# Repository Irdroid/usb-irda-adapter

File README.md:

# usb-irda-adapter
turns a USB port into an IrDA compliant infrared port for communication with IrDA devices on more recent operating systems

The USB irDA adapter is compatible with Windows 7, 10, 11 and Linux (older kernel versions, because the irDA stack was removed in recent kernel versions). 

Allows you to interface with irDA compliant devices, such as dive computers, medical instruments, power meters and more.

- Supports irDa SIR protocol (irDa spec. 1.3 )
- Supports Baud rates from 9600 to 115200
- Drivers for MS Windows 11 and 10
- USB 2.0 interface to the Host system.
- 2 meters line-of-sight irDa communication

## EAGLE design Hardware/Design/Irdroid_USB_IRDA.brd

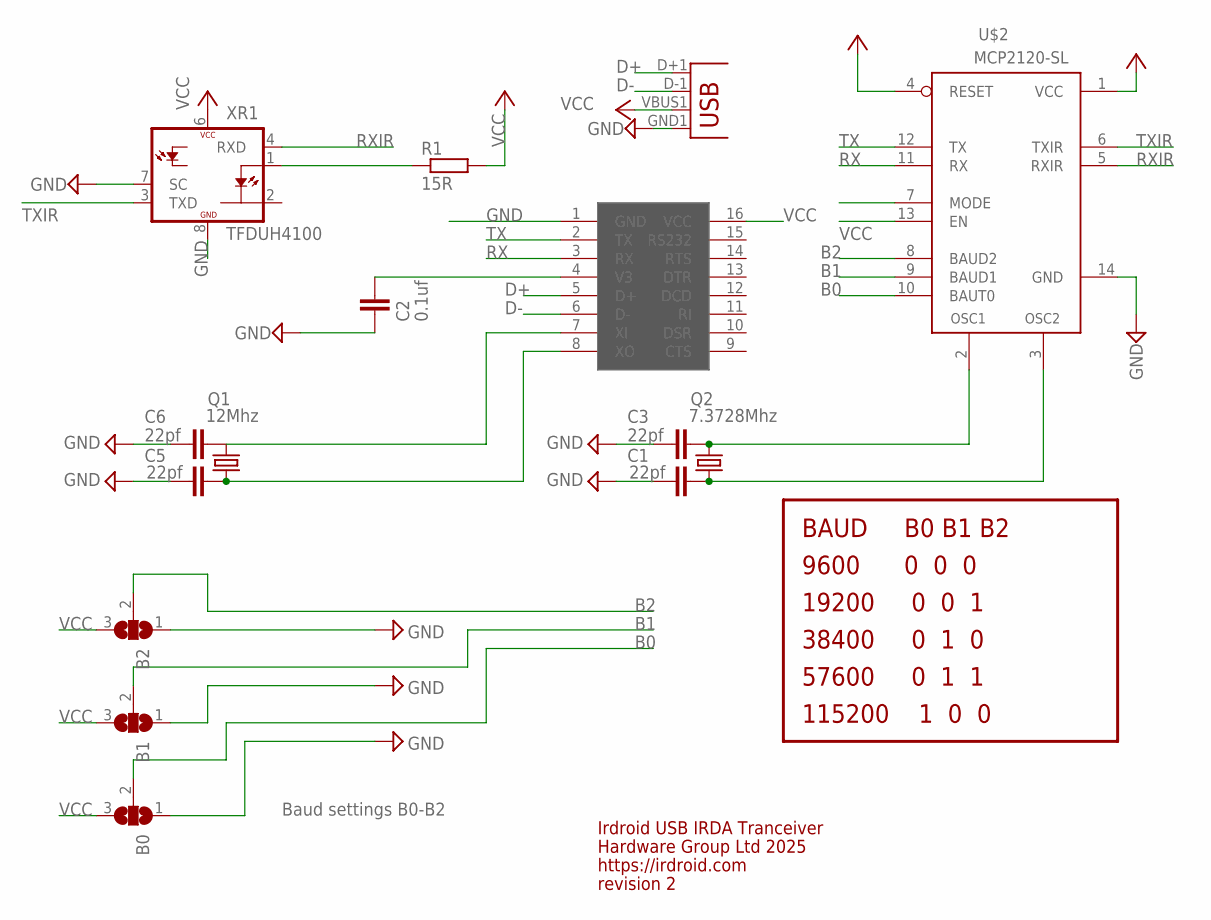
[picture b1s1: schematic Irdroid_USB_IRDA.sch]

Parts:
B0, B1, B2: SJ2W; SJ_2
C1, C3, C5, C6: 22pf; C603
C2: 0.1uf; C603
JP2: USBA-SMD-MALE; USB-A-SMT-MALE
Q1: 12Mhz; HC49UP
Q2: 7.3728Mhz; HC49UP
R1: 15R; R0603
U$1: ch; SOIC16
U$2: MCP2120-SL; SO-14
XR1: TFDUH4100; TFDU4-HOR

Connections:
B0: B0.2, U$2.10 (BAUT0)
B1: B1.2, U$2.9 (BAUD1)
B2: B2.2, U$2.8 (BAUD2)
D+: JP2.D+1 (D+), U$1.5 (D+)
D-: JP2.D-1 (D-), U$1.6 (D-)
GND: B0.1, B1.1, B2.1, C1.2, C2.2, C3.2, C5.2, C6.2, JP2.GND1 (GND), U$1.1 (GND), U$2.14 (GND), XR1.7 (SC), XR1.8 (GND)
unnamed: C5.1, Q1.1, U$1.8 (XO)
unnamed: C3.1, Q2.2, U$2.2 (OSC1)
unnamed: C6.1, Q1.2, U$1.7 (XI)
unnamed: C1.1, Q2.1, U$2.3 (OSC2)
unnamed: C2.1, U$1.4 (V3)
unnamed: R1.1, XR1.1 (IRED-A)
RX: U$1.3 (RX), U$2.11 (RX)
RXIR: U$2.5 (RXIR), XR1.4 (RXD)
TX: U$1.2 (TX), U$2.12 (TX)
TXIR: U$2.6 (TXIR), XR1.3 (TXD)
VCC: B0.3, B1.3, B2.3, JP2.VBUS1 (VBUS), R1.2, U$1.16 (VCC), U$2.1 (VCC), U$2.4 (RESET), U$2.7 (MODE), U$2.13 (EN), XR1.6 (VCC)

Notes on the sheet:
Hardware Group Ltd 2025
Irdroid USB IRDA Tranceiver
https://irdroid.com
Baud settings B0-B2
revision 2
9600 0 0 0
19200 0 0 1
38400 0 1 0
57600 0 1 1
115200 1 0 0
BAUD B0 B1 B2

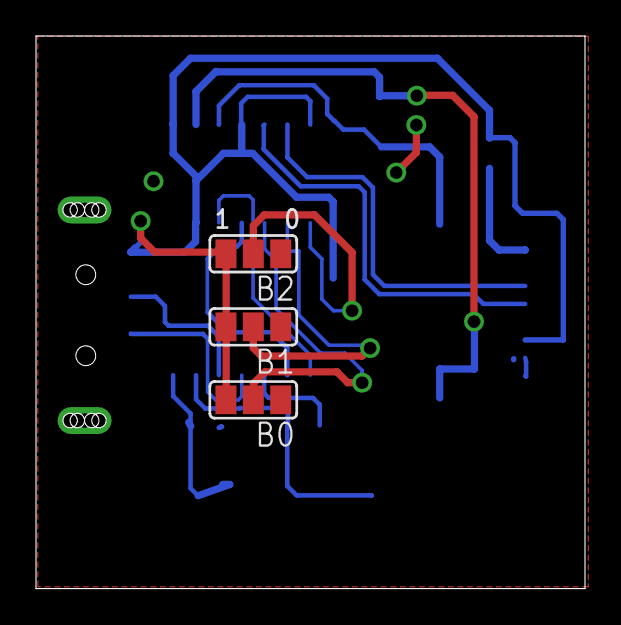
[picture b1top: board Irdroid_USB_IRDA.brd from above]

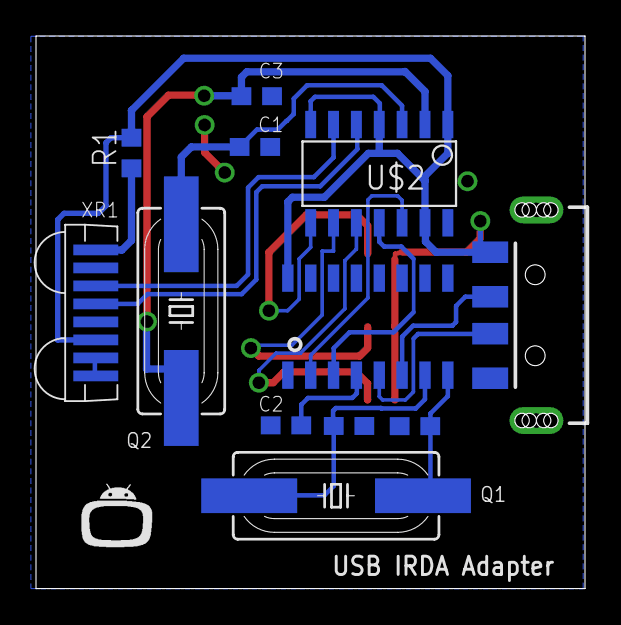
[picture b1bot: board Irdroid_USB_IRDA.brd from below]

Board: 2 copper layers, 30.5 x 30.7 mm, 15 parts (12 on the bottom side), 17 nets.

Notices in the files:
parts and their libraries:
SparkFun-Connectors: Licensing: CC v3.0 Share-Alike You are welcome to use this library for commercial purposes.
